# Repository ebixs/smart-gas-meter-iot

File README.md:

<!--
  Smart Gas Meter IoT
  Languages: English | فارسی | Deutsch
-->

<div align="center">

# Smart Gas Meter IoT

### A modular, safety-conscious smart metering research prototype

**Embedded Systems · Custom PCB · Cellular IoT · Automated Billing · Data Analytics**

<p>

</p>

[Overview](#english) · [فارسی](#فارسی) · [Deutsch](#deutsch) · [Architecture](#architecture) · [Safety](#safety)

[Project site](https://ebixs.github.io/smart-gas-meter-iot/) · [Interactive Project Gallery](hardware/visualization/project-gallery.html) · [3D Concept View](hardware/visualization/smart-gas-meter-exploded.html) · [Visual Design Notes](hardware/visualization/README.md) · [Requirements](docs/requirements.md) · [Architecture Details](docs/architecture.md) · [Development API](docs/api-development.md) · [Production Architecture](docs/production-product-architecture.md) · [Design Decisions v1](hardware/design-decisions-v1.md) · [Release Readiness](hardware/release-readiness.md) · [Pinout & Test Points](hardware/pinout-and-testpoints-v0.2.md) · [AI, Billing & Tamper Requirements](docs/ai-billing-and-tamper-requirements.md) · [Telemetry Contract](docs/telemetry-contract.md) · [Telemetry JSON Schema](schemas/telemetry.schema.json) · [Board v0.1 Design](hardware/board-v0.1-design.md) · [Schematic Plan](hardware/board-v0.2-schematic-plan.md) · [Cellular Modem Interface](hardware/modem-daughterboard-interface.md) · [Board BOM](hardware/BOM-board-v0.1.md) · [Board Netlist Draft](hardware/board-v0.1-netlist-draft.csv) · [Native KiCad Schematic v0.2](hardware/kicad/smart_gas_meter_iot.kicad_sch) · [Schematic PDF](hardware/kicad/exports/smart_gas_meter_iot-schematic.pdf) · [CAD Reference Attribution](hardware/kicad/REFERENCE_ATTRIBUTION_AND_STATUS.md) · [v0.2 Netlist Draft](hardware/kicad/board-v0.2-netlist-draft.csv) · [v0.2 PCB Layout Plan](hardware/kicad/board-v0.2-layout-plan.md) · [PCB Layout Checklist](hardware/board-v0.1-layout-checklist.md) · [Bring-up Test Plan](hardware/board-v0.1-bringup-test-plan.md) · [Initial BOM](hardware/BOM-draft.md) · [Pulse Simulator Spec](hardware/pulse-simulator-spec.md) · [Software Simulator](simulator/pulse_simulator.py) · [Send Synthetic Data to API](simulator/push_to_api.py)

</div>

---

## Showcase

<p align="center">
  
  <br>
  <sub><a href="hardware/visualization/media/sgm-launch-film.mp4">30-second film (MP4)</a> · <a href="https://ebixs.github.io/smart-gas-meter-iot/">project site</a> · all data synthetic · bench prototype</sub>
</p>

| | What it is | Where |
|---|---|---|
| **Fleet console** | 240 simulated meters: readings, self-read invoices, forecasts, alerts | [`docs/dashboard`](docs/dashboard/index.html) · [live](https://ebixs.github.io/smart-gas-meter-iot/dashboard/) |
| **How a pulse works** | Interactive isometric figure: drums, reed pulser, cable, SGM display | [`hardware/visualization/anatomy`](hardware/visualization/anatomy/build.mjs) · [live](https://ebixs.github.io/smart-gas-meter-iot/anatomy/pulse-anatomy-light.html) |
| **Invoice check** | Scan an invoice's QR token, see what the issuer billed | [`docs/verify`](docs/verify/index.html) · [live](https://ebixs.github.io/smart-gas-meter-iot/verify/) |
| **Firmware** | ESP32-S3: debounced reed input, power-safe counter, Jalali self-reading, LTE + SMS fallback | [`firmware/`](firmware/README.md) |
| **Analytics & billing** | Fleet simulator, forecasts (WAPE 9.5 %), six fault detectors, bilingual PDF invoices | [`analytics/`](analytics/) · [report](docs/analytics/REPORT.md) |
| **Hardware** | KiCad 9 schematic, routed 4-layer PCB, BOM, v0.3 power/modem decisions | [`hardware/kicad`](hardware/kicad/) · [decisions](docs/hardware-decisions.md) |
| **Film source** | Code-drawn 30 s film, deterministic frame capture | [`media/film`](media/film/BRIEF.md) |

> **Bench only.** The pulse input takes a synthetic 3.3 V signal; never connect a live gas meter, gas line, valve, mains or field wiring. An analytics alert is not proof of a leak. Invoice prices are illustrative.
>
> **فقط روی میز آزمایش.** ورودی پالس فقط سیگنال مصنوعی ۳٫۳ ولت می‌پذیرد؛ هرگز به کنتور، لوله گاز، شیر، برق شهر یا سیم‌کشی میدانی وصل نشود. هشدار تحلیلی اثبات نشت گاز نیست و قیمت‌های قبض نمونه‌اند.

---

## 🇬🇧 English

### Overview

**Smart Gas Meter IoT** is a proposed end-to-end prototype for exploring how embedded electronics, simulated meter pulses, cellular connectivity, and a Python backend can work together to monitor consumption and prepare billing records.

The project is being developed as a practical engineering portfolio: from circuit and PCB design to firmware, data services, a dashboard, and analytics. **Built so far:** KiCad schematic and routed PCB, ESP32-S3 bench firmware, telemetry contract v2 with a batch API, the analytics and billing pipeline, a fleet console and an invoice verification page (see Showcase). **Not done:** a fabricated and flashed board, field trials, any certification. Anything not listed as built is still a plan.

### Current engineering baseline

- ESP32-S3-WROOM-1-N8 is a candidate controller, not a frozen component choice.
- Cellular communication is planned through a separate modem interface so the modem can be selected after checking the target region, operator, bands and certification path.
- The board direction is a larger, test-friendly four-layer design, subject to electrical and layout review.
- Early tests must use synthetic pulses and isolated low-voltage circuits only.
- AI anomaly flags are advisory and cannot establish that a gas leak exists.
- Billing output remains a prototype report until metrology and legal requirements are established.

### Planned capabilities

- Embedded controller, local storage, timekeeping and status indicators.
- Safe pulse simulation without connecting to a live gas meter.
- Cellular telemetry with local queueing and retry after reconnect.
- Python API, database, device records and validation.
- Traceable draft invoices with tariff versioning and QR verification.
- Consumption trends, forecasts, anomaly flags, tamper/fault events and device-health monitoring.
- Engineering documentation, native schematic, PCB layout, 3D assembly views and test plans.

### Development roadmap

- [x] Draft initial requirements and system interfaces.
- [x] Specify simulator acceptance tests and add a software telemetry fixture.
- [x] Add unit tests for the simulator and GitHub Actions CI workflow.
- [x] Define the versioned telemetry contract and JSON Schema.
- [x] Document the initial controller/board concept, cellular interface, product architecture, pinout proposal and release gates.
- [x] Add a standalone interactive isometric concept illustration (not CAD-derived or fabrication-ready).
- [x] Rebuild the native KiCad schematic from a reviewed design table (v0.2): KiCad 9 ERC 0 errors / 0 warnings, exported netlist checked pin-by-pin against the design.
- [x] Select exact, orderable parts (MPN + LCSC) checked against datasheets; schematic freeze candidate v0.2-rc1 ([part selection](hardware/kicad/PART_SELECTION.md)).
- [ ] Second-engineer sign-off of the schematic freeze.
- [x] Create a routed 4-layer KiCad PCB from the schematic: KiCad 9 DRC 0 violations / 0 unconnected / 0 schematic-parity issues, with CAD-derived 3D renders ([PCB design](hardware/kicad/PCB_DESIGN.md)).
- [ ] Hand-tune the USB pair, review the power layout and DFM, and get second-engineer sign-off before ordering boards.
- [ ] Complete BOM with exact parts, footprints and approved alternates.
- [x] Run electrical-rule and design-rule checks (ERC and DRC clean; reports in `hardware/kicad/exports/`).
- [x] Export Gerbers, drill, BOM and pick-and-place files as **review artefacts** (not released for fabrication).
- [x] Add a development-only FastAPI + SQLite ingestion API with duplicate-safe records, bearer-token protection, pulse-delta reporting and a local dashboard (`/dashboard`).
- [ ] Add per-device identity/credentials, production database hardening, firmware, billing and analytics.
- [ ] Run recorded low-voltage bench tests and later region-specific radio validation.
- [ ] Complete qualified safety, metrology, EMC, radio, cybersecurity and regulatory reviews.

---

## 🇮🇷 فارسی

<div dir="rtl" align="right">

### معرفی پروژه

**کنتور گاز هوشمند اینترنت اشیا (Smart Gas Meter IoT)** پروژه‌ای برای ارتقای یک ایده سخت‌افزاری قدیمی با رویکرد مهندسی جدید است؛ از طراحی برد و ارتباط سلولی تا ثبت داده، تحلیل مصرف و تولید گزارش صورتحساب.

### تصمیم‌های طراحی فعلی

- میکروکنترلر ESP32-S3-WROOM-1-N8 گزینه اولیه است و تا بررسی مدار نهایی، قطعه قطعی محسوب نمی‌شود.
- مودم سیم‌کارتی به‌صورت ماژول جداشدنی طراحی می‌شود تا انتخاب مدل به پوشش شبکه، اپراتور، باندها و تأییدیه‌ها وابسته بماند.
- جهت طراحی برد، نمونه‌ای بزرگ‌تر و چهارلایه با نقاط تست فراوان است؛ تعداد لایه‌ها و ابعاد پس از طراحی و بررسی نهایی می‌شود.
- آزمون اولیه فقط با پالس مصنوعی و مدار کم‌ولتاژ ایزوله انجام می‌شود.
- تحلیل ناهنجاری مصرف به‌تنهایی اثبات‌کننده نشت گاز نیست.
- صورتحساب تا تعیین الزامات قانونی و اندازه‌گیری، گزارش آزمایشی است.

### وضعیت واقعی پروژه

مستندات معماری، نیازمندی‌ها، رابط مودم، نگاشت اولیه پایه‌ها و برنامه آمادگی ساخت در مخزن قرار گرفته‌اند. شماتیک بومی KiCad نسخه v0.2 به‌صورت کنترل‌شده از نو ساخته شده و ERC آن بدون خطاست. PCB چهارلایه هم از روی همین شماتیک مسیرکشی شده و DRC آن بدون خطا و کاملاً منطبق با شماتیک است. با این حال **فایل‌های ساخت فقط برای بازبینی هستند** و پیش از سفارش، مسیر USB، چیدمان تغذیه و بررسی مهندس دوم باید تکمیل شود؛ بنابراین پروژه هنوز آماده سفارش PCB یا مونتاژ نیست.

### نقشه راه

- [x] تدوین نیازمندی‌ها، معماری و قرارداد داده.
- [x] ساخت شبیه‌ساز نرم‌افزاری، ابزار ارسال داده مصنوعی به API و آزمون‌های خودکار.
- [x] مستندسازی تصمیم‌های اولیه برد، رابط مودم، نقاط تست و معیارهای آماده‌سازی ساخت.
- [x] افزودن API آزمایشی FastAPI و SQLite با توکن دسترسی، جلوگیری از تکرار، گزارش اختلاف شمارنده پالس و داشبورد محلی (`/dashboard`).
- [ ] افزودن هویت و اعتبارنامه مستقل برای هر دستگاه، سخت‌سازی پایگاه داده، فریم‌ور و صورتحساب واقعی.
- [x] بازسازی شماتیک بومی KiCad از جدول طراحی (v0.2): ERC در KiCad 9 بدون خطا و هشدار، و تطبیق پایه‌به‌پایه نت‌لیست با طراحی.
- [x] انتخاب قطعات دقیق و قابل سفارش (MPN و کد LCSC) با بررسی دیتاشیت؛ نسخه‌ی کاندید فریز شماتیک v0.2-rc1.
- [ ] تأیید نهایی فریز شماتیک توسط یک مهندس دوم.
- [x] طراحی و مسیرکشی PCB چهارلایه و بررسی DRC (بدون خطا، بدون اتصال باز و منطبق با شماتیک).
- [x] استخراج نمای سه‌بعدی از مدل واقعی PCB.
- [ ] تکمیل BOM، فوت‌پرینت‌ها و قطعات جایگزین.
- [x] تولید Gerber، فایل سوراخ‌کاری و فایل‌های مونتاژ برای بازبینی (هنوز برای سفارش ساخت تأیید نشده).
- [ ] اجرای آزمون‌های ثبت‌شده با مدار کم‌ولتاژ.
- [ ] ارزیابی تخصصی ایمنی، اندازه‌گیری، رادیویی، EMC و مقررات پیش از استفاده عملیاتی.

</div>

---

## 🇩🇪 Deutsch

Smart Gas Meter IoT is a modular engineering prototype for simulated pulse acquisition, cellular telemetry, data analysis and draft billing. The repository documents the intended design and separates documented proposals from implemented and verified hardware.

The current baseline proposes an ESP32-S3 controller, a modular cellular interface and a larger test-friendly PCB. A development-only FastAPI + SQLite service and local dashboard now accept/view synthetic telemetry, require a shared bearer token for data endpoints, and reject conflicting duplicate sequences. It is not production-secure and does not yet provide per-device credentials. A rebuilt native KiCad schematic (freeze candidate v0.2-rc1, exact parts selected) passes KiCad 9 ERC with no violations, but awaits second-engineer sign-off; a routed 4-layer PCB passes DRC with schematic parity and has CAD-derived 3D renders; Gerbers exist as review artefacts only, pending USB-pair tuning, power-layout/DFM review and sign-off. Only isolated low-voltage laboratory tests using synthetic pulses are in scope at this stage.

---

## System architecture / معماری سیستم

```mermaid
flowchart LR
    A["Pulse Simulator"] --> B["Embedded Controller"]
    B --> C["Local Storage"]
    B --> D["Cellular IoT"]
    D --> E["Python API"]
    E --> F[("Database")]
    F --> G["Billing Service"]
    F --> H["Dashboard & Analytics"]
```

This is the planned architecture, not a claim that all components have been implemented.

## Safety and scope / ایمنی

- Laboratory prototype only. Use simulated pulses and low-voltage test circuits.
- Do not connect this prototype to a live gas line, operational meter, mains wiring or unknown field signals.
- This project is not a certified measuring instrument, leak detector, billing authority or safety device.
- Real deployment requires qualified review and applicable metrology, gas-safety, radio, EMC, cybersecurity and local regulatory compliance.
- No component ordering or fabrication is authorized without explicit owner approval.

## Project history / سابقه پروژه

In 1396 SH (2017–2018), the project owner personally designed and built an original smart gas meter prototype for Iran Gas Company in Shahrekord, Chaharmahal and Bakhtiari Province, Iran. This repository documents a modernized development effort; historical work must not be confused with new features that remain unimplemented or untested.

## License

No license has been selected yet. Until a license is added, the repository should not be assumed to grant permission to reuse, modify or distribute its contents.

### v0.2 hardware design drafts
- [PCB design & 3D renders](hardware/kicad/PCB_DESIGN.md) · [DRC report](hardware/kicad/exports/pcb/drc-kicad-9.rpt) · [Gerbers (review only)](hardware/kicad/exports/pcb/gerbers/)
- [Native schematic v0.2-rc1 (PDF)](hardware/kicad/exports/smart_gas_meter_iot-schematic.pdf) · [KiCad ERC report](hardware/kicad/exports/erc-kicad-9.0.3.rpt) · [BOM](hardware/kicad/exports/BOM-v0.2-rc1.md) · [JLCPCB BOM (CSV)](hardware/kicad/exports/BOM-v0.2-rc1-jlcpcb.csv) · [Part selection](hardware/kicad/PART_SELECTION.md)
- [Design table — single source of truth](hardware/kicad/design_v02.py) and [how the schematic is generated and verified](hardware/kicad/README.md)
- [Candidate pin-to-net map (CSV)](hardware/kicad/board-v0.2-netlist-draft.csv)
- [PCB placement and routing plan](hardware/kicad/board-v0.2-layout-plan.md)
- [Native KiCad delivery gate](hardware/kicad/NATIVE_CAD_DELIVERY_GATE.md)

Schematic (ERC-clean) and routed PCB (DRC-clean, schematic parity) exist for review. Fabrication still waits on USB-pair tuning, power-layout/DFM review, land-pattern checks and sign-off.

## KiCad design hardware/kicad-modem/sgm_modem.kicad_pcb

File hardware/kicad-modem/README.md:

# Modem daughterboard v0.1 — Quectel EC200U-EU (KiCad)

**Status: v0.1-draft — engineering draft, NOT fabrication ready.** The schematic follows the Quectel EC200U Series
Hardware Design V1.0; the PCB is a 4-layer layout study. **The EC200U footprint is provisional**: its pad geometry and
the pad that carries each pin number are placeholders built from the partial dimensions in the hardware design guide.
It must be replaced by Quectel's *EC200U Series Footprint & Part* file, and the board re-placed and re-routed, before
any layout review or order. Bench-only: `MODEM_VIN` comes from a current-limited 3.8 V supply. Never connect any of
this to a live gas meter, gas line, valve, mains or field wiring.

The board plugs onto the carrier board's modem header **J6** (carrier v0.2, `hardware/kicad/`) with a socket **J1**
on its underside, pin for pin: `1 MODEM_VIN · 2 GND · 3 MODEM_TXD · 4 MODEM_RXD · 5 MODEM_EN · 6 MODEM_RESET ·
7 MODEM_STATUS · 8 GND` (3.3 V logic). It is the "replaceable modem board" of the hardware decisions.

## What is here

| Path | Purpose |
|---|---|
| `design_modem_v01.py` | **Single source of truth**: every part, value, footprint and pin → net assignment (same `Part` API as the carrier's `design_v02.py`) |
| `tools/generate_schematic.py` | Writes the schematic, project file and project-local libraries; reuses the carrier's sheet writer unchanged; generates the `EC200U` symbol and the **provisional** footprint |
| `sgm_modem.kicad_sch` / `.kicad_pro` | Native KiCad schematic (KiCad 7 format; opens in KiCad 7, 8, 9) |
| `lib/sgm_modem.kicad_sym`, `lib/SGMM.pretty/`, `lib/3d/` | Project-local symbols, footprints and STEP models (nickname `SGMM`) |
| `pcb_layout_modem_v01.py` | Placement table (75 × 50 mm, 4 layers) |
| `tools/build_pcb.py` | Builds the board with KiCad's `pcbnew` module, fans ground and VBAT pads out to their planes, autoroutes with Freerouting, stitches the ground pours and writes a DRC report |
| `sgm_modem.kicad_pcb` | The routed layout study |
| `check_netlist_matches_design.py` | Netlist vs. design, pin by pin, plus J1 pin-out = carrier J6 |
| `tests/` | Design invariants (no 3V3 on the modem, open-collector PWRKEY/RESET_N, every 1.8 V output shifted, …) |
| `exports/` | Schematic PDF, netlist, DRC report, layer artwork |

## Circuit (from the EC200U hardware design guide)

1. **VBAT** — `MODEM_VIN` (3.3–4.3 V, 3.8 V nominal, up to 2 A bursts) feeds VBAT_RF (57, 58) and VBAT_BB (59, 60).
   Two 100 µF low-ESR tantalum capacitors, a 100 nF / 33 pF / 10 pF MLCC set at each pin pair, and a TVS diode with
   ≥ 4.7 V stand-off (to be selected). On the PCB the whole inner layer In2 is the VBAT plane (the guide asks for
   ≥ 2–2.5 mm VBAT traces). J2 is an optional direct VBAT input, not fitted: never run it in parallel with carrier J7.
2. **PWRKEY / RESET_N** — open-collector MMBT3904 drivers (4.7 kΩ base resistor, 47 kΩ base pull-down) from
   `MODEM_EN` / `MODEM_RESET`. The carrier's 100 kΩ pull-downs keep the module off while the ESP32 boots.
   Switching on or off needs PWRKEY low for ≥ 2 s.
3. **Level shifting** — the module's UART and STATUS are 1.8 V. Three N-MOSFET shifters with their gates on
   `VDD_EXT` (the module's own 1.8 V output, 2.2 µF) and 10 kΩ pull-ups on the 1.8 V side. Candidate FET:
   Diodes DMG2302U (V<sub>GS(th)</sub> ≤ 1.0 V); a BSS138 is marginal with a 1.8 V gate.
4. **(U)SIM** — JAE SF53S006VCBR2000 micro-SIM, 0 Ω series resistors, 33 pF on each line, 10 kΩ pull-up on DATA,
   100 nF on USIM_VDD and a TI ESD224 array (0.5 pF; the guide's limit is 15 pF).
5. **Antenna** — ANT_MAIN on a short 50 Ω line (net class RF, 0.35 mm over the In1 ground plane — confirm with the
   fabricator's stack-up) to a Hirose u.FL, with a π network (0 Ω + two not-mounted shunts).
6. **Network LED** — NET_STATUS drives a green LED through a transistor, about 1.8 mA from VBAT.
7. **Bench access** — test pads for the module USB (VBUS, D+, D−) and the 1.8 V debug UART; solder jumper JP1 with
   4.7 kΩ to `VDD_EXT` forces USB download mode when closed before power-up (open by default).

## Review items (open)

- **Footprint**: replace the provisional EC200U footprint with Quectel's file; then re-place and re-route.
- **MCU-side pull-ups**: J6 carries no 3.3 V rail, so `MODEM_RXD` and `MODEM_STATUS` rely on the ESP32's internal
  pull-ups (firmware must enable them). Alternative: add 3V3 to the next carrier revision's modem header.
- **TVS selection** for VBAT, exact MPNs for the tantalum capacitors and the MOSFETs.
- **Header current**: one 2.54 mm pin carries `MODEM_VIN` bursts of up to 2 A; check the socket rating or use J2.
- **RF line width** against the real stack-up; tune the π network with the chosen antenna.

## Verification (2026-10-26, KiCad 7.0.11 here; CI repeats ERC/DRC with KiCad 9)

| Check | Result |
|---|---|
| Netlist vs. design (`check_netlist_matches_design.py`) | 55 parts, 35 nets, 190 pin connections match; J1 = carrier J6 |
| Schematic ↔ design sync (`generate_schematic.py --check`) | committed file matches a fresh generation |
| Design invariants (`python3 -m unittest discover -s hardware/kicad-modem/tests`) | pass |
| DRC (KiCad 7 `pcbnew`, `exports/drc-kicad-7.rpt`) | 0 violations, 0 unconnected pads |
| ERC + DRC with schematic parity, KiCad 9 (CI `hardware-cad-check.yml`, PR #8) | ERC pass; DRC 0 violations, 0 unconnected, 0 footprint errors |

A clean DRC here only proves the layout is consistent with the **provisional** footprint; it says nothing about the real module pads.

## Regenerate

```bash
python3 hardware/kicad-modem/tools/generate_schematic.py [--kicad-3d /path/to/kicad-packages3D]
python3 hardware/kicad-modem/tools/build_pcb.py --route          # needs Java 21 and freerouting.jar (v2.1)
kicad-cli sch export netlist -o /tmp/modem.net hardware/kicad-modem/sgm_modem.kicad_sch
python3 hardware/kicad-modem/check_netlist_matches_design.py /tmp/modem.net
python3 -m unittest discover -s hardware/kicad-modem/tests
```

The board's exploded 3D model is in `hardware/visualization/boards/modem.html`, and the schematic can be explored
net by net in `hardware/visualization/schematic/index.html`.

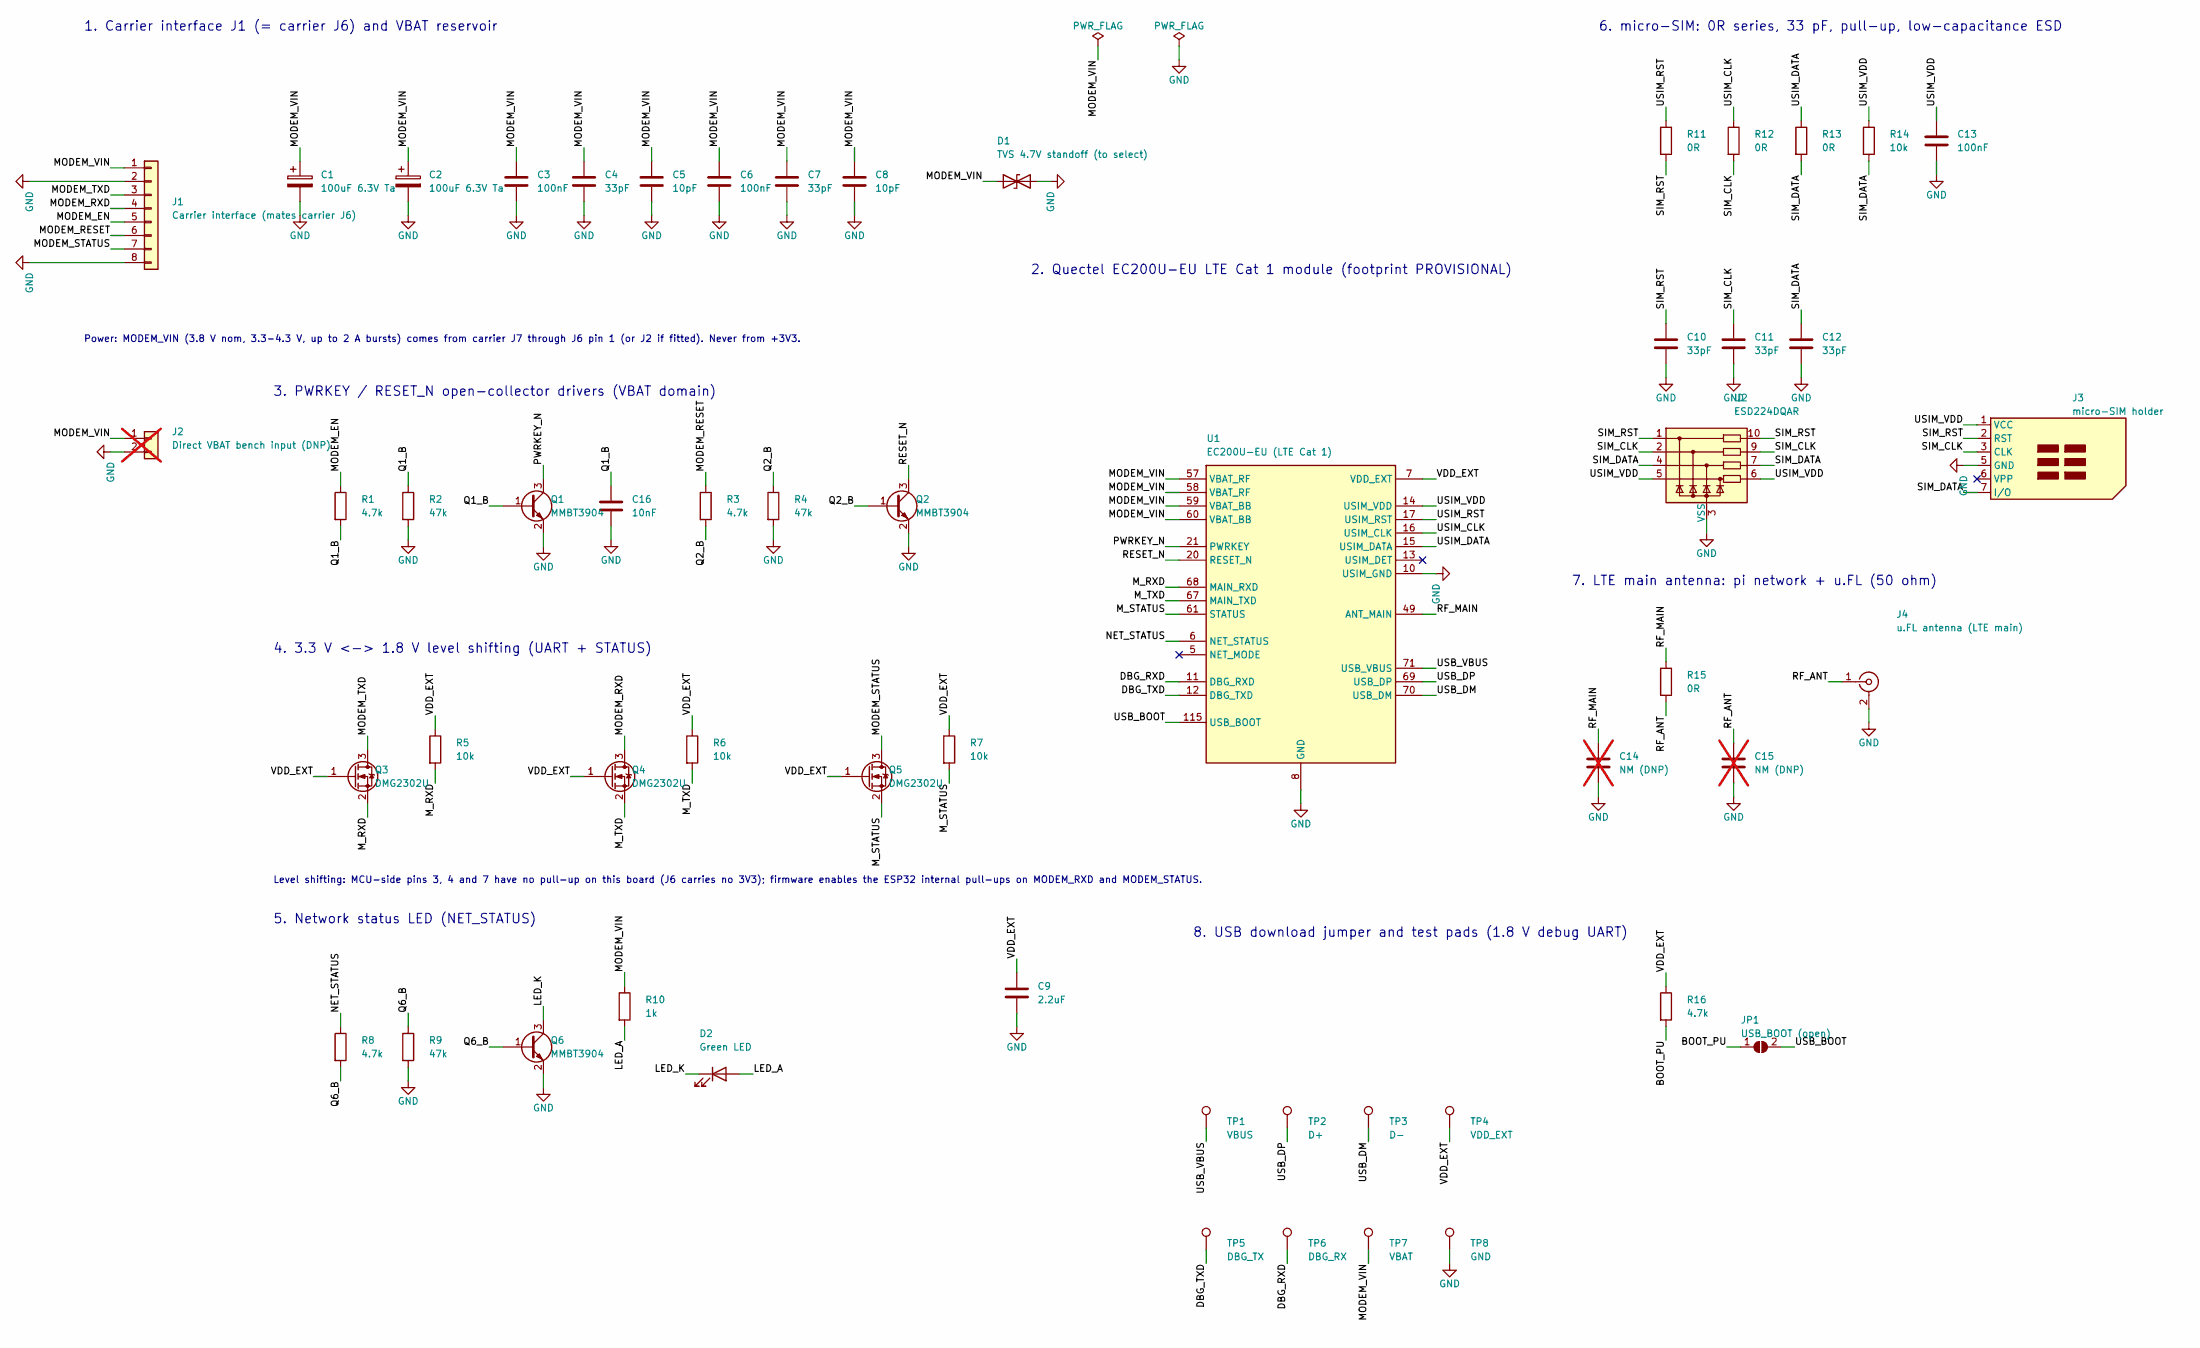
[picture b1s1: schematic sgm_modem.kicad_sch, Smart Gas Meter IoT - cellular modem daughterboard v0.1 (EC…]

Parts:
C1, C2: 100uF 6.3V Ta; CP_EIA-3528-21_Kemet-B; MPN TBD
C3, C6, C13: 100nF; C_0402_1005Metric; MPN TBD
C4, C7, C10, C11, C12: 33pF; C_0402_1005Metric; MPN TBD
C5, C8: 10pF; C_0402_1005Metric; MPN TBD
C9: 2.2uF; C_0402_1005Metric; MPN TBD
C14, C15: NM (DNP); C_0402_1005Metric; MPN TBD; not fitted
C16: 10nF; C_0402_1005Metric; MPN TBD
D1: TVS 4.7V standoff (to select); D_SMB; MPN TBD
D2: Green LED; LED_0603_1608Metric; MPN TBD
J1: Carrier interface (mates carrier J6); PinSocket_1x08_P2.54mm_Vertical; MPN generic
J2: Direct VBAT bench input (DNP); PinHeader_1x02_P2.54mm_Vertical; MPN generic; not fitted
J3: micro-SIM holder; microSIM_JAE_SF53S006VCBR2000; MPN JAE SF53S006VCBR2000
J4: u.FL antenna (LTE main); U.FL_Hirose_U.FL-R-SMT-1_Vertical; MPN Hirose U.FL-R-SMT-1
JP1: USB_BOOT (open); SolderJumper-2_P1.3mm_Open_RoundedPad1.0x1.5mm; MPN generic
Q1, Q2, Q6: MMBT3904; SOT-23; MPN TBD
Q3, Q4, Q5: DMG2302U; SOT-23; MPN TBD
R1, R3, R8, R16: 4.7k; R_0402_1005Metric; MPN TBD
R2, R4, R9: 47k; R_0402_1005Metric; MPN TBD
R5, R6, R7, R14: 10k; R_0402_1005Metric; MPN TBD
R10: 1k; R_0402_1005Metric; MPN TBD
R11, R12, R13, R15: 0R; R_0402_1005Metric; MPN TBD
TP1: VBUS; TestPoint_Pad_D1.0mm; MPN generic
TP2: D+; TestPoint_Pad_D1.0mm; MPN generic
TP3: D-; TestPoint_Pad_D1.0mm; MPN generic
TP4: VDD_EXT; TestPoint_Pad_D1.0mm; MPN generic
TP5: DBG_TX; TestPoint_Pad_D1.0mm; MPN generic
TP6: DBG_RX; TestPoint_Pad_D1.0mm; MPN generic
TP7: VBAT; TestPoint_Pad_D1.0mm; MPN generic
TP8: GND; TestPoint_Pad_D1.0mm; MPN generic
U1: EC200U-EU (LTE Cat 1); Quectel_EC200U_PROVISIONAL; MPN Quectel EC200U-EU (candidate)
U2: ESD224DQAR; USON-10_2.5x1.0mm_P0.5mm; MPN Texas Instruments ESD224DQAR (candidate)

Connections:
/BOOT_PU: JP1.1 (A), R16.2
/DBG_RXD: TP6.1, U1.11 (DBG_RXD)
/DBG_TXD: TP5.1, U1.12 (DBG_TXD)
/LED_A: D2.2 (A), R10.2
/LED_K: D2.1 (K), Q6.3 (C)
/MODEM_EN: J1.5, R1.1
/MODEM_RESET: J1.6, R3.1
/MODEM_RXD: J1.4, Q4.3 (D)
/MODEM_STATUS: J1.7, Q5.3 (D)
/MODEM_TXD: J1.3, Q3.3 (D)
/MODEM_VIN: C1.1, C2.1, C3.1, C4.1, C5.1, C6.1, C7.1, C8.1, D1.1 (A1), J1.1, J2.1, R10.1, TP7.1, U1.57 (VBAT_RF), U1.58 (VBAT_RF), U1.59 (VBAT_BB), U1.60 (VBAT_BB)
/M_RXD: Q3.2 (S), R5.2, U1.68 (MAIN_RXD)
/M_STATUS: Q5.2 (S), R7.2, U1.61 (STATUS)
/M_TXD: Q4.2 (S), R6.2, U1.67 (MAIN_TXD)
/NET_STATUS: R8.1, U1.6 (NET_STATUS)
/PWRKEY_N: Q1.3 (C), U1.21 (PWRKEY)
/Q1_B: C16.1, Q1.1 (B), R1.2, R2.1
/Q2_B: Q2.1 (B), R3.2, R4.1
/Q6_B: Q6.1 (B), R8.2, R9.1
/RESET_N: Q2.3 (C), U1.20 (RESET_N)
/RF_ANT: C15.1, J4.1 (In), R15.2
/RF_MAIN: C14.1, R15.1, U1.49 (ANT_MAIN)
/SIM_CLK: C11.1, J3.3 (CLK), R12.2, U2.2, U2.9
/SIM_DATA: C12.1, J3.7 (I/O), R13.2, R14.2, U2.4, U2.7
/SIM_RST: C10.1, J3.2 (RST), R11.2, U2.1, U2.10
/USB_BOOT: JP1.2 (B), U1.115 (USB_BOOT)
/USB_DM: TP3.1, U1.70 (USB_DM)
/USB_DP: TP2.1, U1.69 (USB_DP)
/USB_VBUS: TP1.1, U1.71 (USB_VBUS)
/USIM_CLK: R12.1, U1.16 (USIM_CLK)
/USIM_DATA: R13.1, U1.15 (USIM_DATA)
/USIM_RST: R11.1, U1.17 (USIM_RST)
/USIM_VDD: C13.1, J3.1 (VCC), R14.1, U1.14 (USIM_VDD), U2.5, U2.6
/VDD_EXT: C9.1, Q3.1 (G), Q4.1 (G), Q5.1 (G), R5.1, R6.1, R7.1, R16.1, TP4.1, U1.7 (VDD_EXT)
GND: C1.2, C2.2, C3.2, C4.2, C5.2, C6.2, C7.2, C8.2, C9.2, C10.2, C11.2, C12.2, C13.2, C14.2, C15.2, C16.2, D1.2 (A2), J1.2, J1.8, J2.2, J3.5 (GND), J3.SH, J4.2 (Ext), Q1.2 (E), Q2.2 (E), Q6.2 (E), R2.2, R4.2, R9.2, TP8.1, U1.8 (GND), U1.9 (GND), U1.10 (USIM_GND), U1.19 (GND), U1.22 (GND), U1.36 (GND), U1.46 (GND), U1.48 (GND), U1.50 (GND), U1.51 (GND), U1.52 (GND), U1.53 (GND), U1.54 (GND), U1.56 (GND), U1.72 (GND), U1.76 (GND), U1.85 (GND), U1.86 (GND), U1.87 (GND), U1.88 (GND), U1.89 (GND), U1.90 (GND), U1.91 (GND), U1.92 (GND), U1.93 (GND), U1.94 (GND), U1.95 (GND), U1.96 (GND), U1.97 (GND), U1.98 (GND), U1.99 (GND), U1.100 (GND), U1.101 (GND), U1.102 (GND), U1.103 (GND), U1.104 (GND), U1.105 (GND), U1.106 (GND), U1.107 (GND), U1.108 (GND), U1.109 (GND), U1.110 (GND), U1.111 (GND), U1.112 (GND), U2.3 (VSS), U2.8 (VSS)

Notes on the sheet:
1. Carrier interface J1 (= carrier J6) and VBAT reservoir
2. Quectel EC200U-EU LTE Cat 1 module (footprint PROVISIONAL)
3. PWRKEY / RESET_N open-collector drivers (VBAT domain)
4. 3.3 V <-> 1.8 V level shifting (UART + STATUS)
5. Network status LED (NET_STATUS)
6. micro-SIM: 0R series, 33 pF, pull-up, low-capacitance ESD
7. LTE main antenna: pi network + u.FL (50 ohm)
8. USB download jumper and test pads (1.8 V debug UART)
Power: MODEM_VIN (3.8 V nom, 3.3-4.3 V, up to 2 A bursts) comes from carrier J7 through J6 pin 1 (or J2 if fitted). Never from +3V3.
Level shifting: MCU-side pins 3, 4 and 7 have no pull-up on this board (J6 carries no 3V3); firmware enables the ESP32 internal pull-ups on MODEM_RXD and MODEM_STATUS.

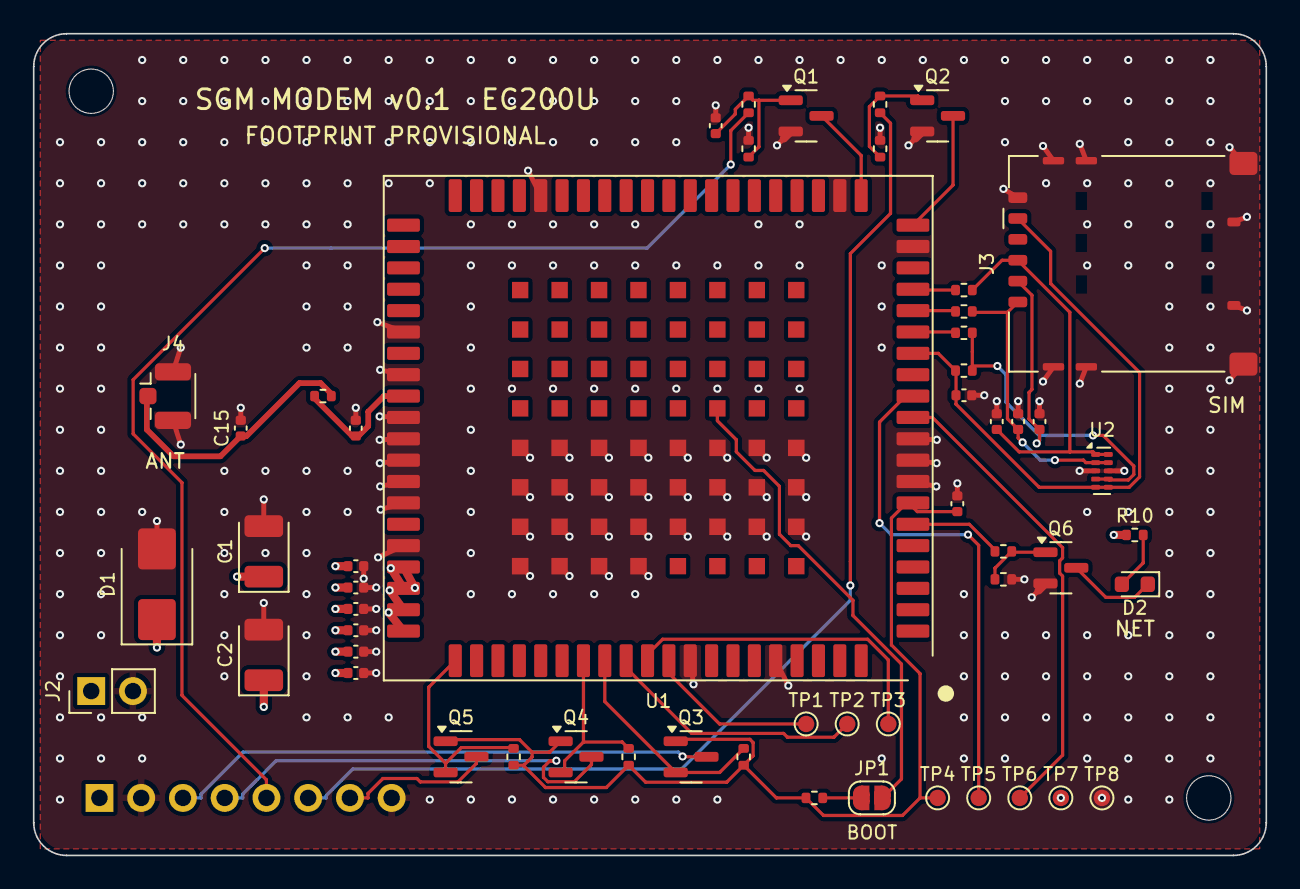
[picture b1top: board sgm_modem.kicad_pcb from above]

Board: 4 copper layers, 75.0 x 50.0 mm, 57 parts (1 on the bottom side), 35 nets.

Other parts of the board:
H1, H2: M2.5; MountingHole_2.7mm_M2.5

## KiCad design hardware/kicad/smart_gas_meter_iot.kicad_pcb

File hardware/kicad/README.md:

# Native KiCad project — carrier board v0.2

**Status: v0.2-rc1 — schematic freeze candidate with exact parts selected ([PART_SELECTION.md](PART_SELECTION.md)). ERC-clean; awaiting second-engineer sign-off. Routed 4-layer PCB is DRC-clean with schematic parity ([PCB_DESIGN.md](PCB_DESIGN.md)); not released for fabrication.**
Bench-only prototype: current-limited low-voltage supply and a synthetic 3.3 V pulse source. Never connect it to a live gas meter, gas line, valve, mains or field wiring.

## What is here

| Path | Purpose |
|---|---|
| `design_v02.py` | **Single source of truth**: every part, value, footprint, selected MPN/LCSC code and pin → net assignment |
| `tools/generate_schematic.py` | Generates the schematic, project file and project-local libraries from `design_v02.py` |
| `smart_gas_meter_iot.kicad_sch` / `.kicad_pro` | Native KiCad schematic (KiCad 7 file format; opens in KiCad 7, 8 and 9) |
| `lib/smart_gas_meter.kicad_sym`, `lib/SGM.pretty/` | Project-local copies of the KiCad 7.0.11 stock symbols/footprints actually used, so CI needs no global libraries |
| `sym-lib-table`, `fp-lib-table` | Project library tables (nickname `SGM`) |
| `tools/export_bom.py` | Writes the review BOM and the JLCPCB assembly BOM from `design_v02.py` |
| `check_netlist_matches_design.py` | Compares a KiCad-exported netlist with `design_v02.py`, pin by pin |
| `check_netlist_invariants.py` | Guardrail for the blocking faults found in the frozen draft (GND on supply rails, shorted capacitors, legacy dev-board headers, modem on 3V3) |
| `pcb_layout_v02.py`, `tools/build_pcb.py` | PCB placement table and KiCad 9 build/autoroute script |
| `smart_gas_meter_iot.kicad_pcb` | Routed 4-layer PCB (source of truth for copper) |
| `tools/export_pcb.sh` | DRC with schematic parity, Gerbers, drill, CPL, layer PDFs, 3D renders → `exports/pcb/` |
| `lib/3d/` | STEP models for every footprint (paths use `${KIPRJMOD}`) |
| `exports/` | Schematic PDF/PNG, KiCad 9 ERC report, exported netlist and review/JLCPCB BOMs for `v0.2-rc1` |
| `archive/v0.2-frozen-2026-10-23/` | The frozen first draft, kept unchanged as evidence (65 ERC messages, +5V/GND short) |

## Circuit summary

1. **USB-C input** — USB 2.0 receptacle (J1), 5.1 kΩ Rd on CC1 and CC2 separately (R1/R2), PTC fuse (F1) from `USB_VBUS` to `+5V`, TVS (D1) on `+5V`, USBLC6-2SC6 ESD array (U2) on D+/D−.
2. **3V3 buck** — AP63203WU-7 (U3) with the datasheet typical application: 10 µF input, 3.9 µH inductor, 2 × 22 µF output, 100 nF bootstrap; EN tied to VIN.
3. **ESP32-S3-WROOM-1-N8** (U1) — 10 µF + 100 nF at 3V3; EN RC 10 kΩ/1 µF per Espressif guidelines; RESET (SW1) and BOOT/GPIO0 (SW2) buttons; native USB on GPIO19/GPIO20.
4. **Synthetic pulse input** (J2 → GPIO4) — 10 kΩ pull-up, 1 kΩ series resistor, optional DNP filter capacitor. 3.3 V logic or dry contact only.
5. **Status LED** on GPIO5. 6. **Tamper switch** input on GPIO15 with pull-up and RC debounce (advisory event only).
7. **I2C expansion** (GPIO6/7, 4.7 kΩ pull-ups) and **debug UART0** header (no power pin, to avoid back-feeding).
8. **Modem daughterboard connector** (J6) — UART on GPIO17/18, EN/RESET/STATUS on GPIO9/10/11 with safe-default pull-downs. `MODEM_VIN` comes from its own bench-supply connector (J7) and is **never** connected to `+3V3`.
9. **Test points** for 5V, 3V3, VBUS, VMODEM, GND (×2), PULSE_IN, EN and BOOT.

Distinct rails in the netlist: `USB_VBUS`, `+5V`, `+3V3`, `GND`, `MODEM_VIN`. Unused module GPIOs carry explicit no-connect flags (strapping pins GPIO3/45/46 stay at their default state).

## Verification evidence (2026-10-24)

| Check | Tool | Result |
|---|---|---|
| ERC | KiCad 9.0.3 `kicad-cli sch erc --exit-code-violations` | **0 errors, 0 warnings**, no exclusions or rule changes ([report](exports/erc-kicad-9.0.3.rpt)) |
| Netlist vs. design | `check_netlist_matches_design.py` | 48 parts, 28 nets, 135 pin connections match; NC pins match exactly |
| Electrical invariants | `check_netlist_invariants.py` | pass (the same checker reports 10 findings on the archived frozen draft) |
| Schematic ↔ design sync | `generate_schematic.py --check` | committed file is byte-identical to a fresh generation |

The CI workflow `hardware-cad-check.yml` repeats all four checks with KiCad 9 on every push that touches `hardware/kicad/`.

## Regenerate and verify locally

```bash
python3 hardware/kicad/tools/generate_schematic.py          # rewrite schematic + libraries from design_v02.py
python3 hardware/kicad/tools/export_bom.py                  # review BOM + JLCPCB BOM
kicad-cli sch erc --exit-code-violations hardware/kicad/smart_gas_meter_iot.kicad_sch   # KiCad 8/9
kicad-cli sch export netlist -o /tmp/sgm.net hardware/kicad/smart_gas_meter_iot.kicad_sch
python3 hardware/kicad/check_netlist_matches_design.py /tmp/sgm.net
python3 hardware/kicad/check_netlist_invariants.py /tmp/sgm.net
python3 -m unittest discover -s hardware/kicad/tests
```

To change the circuit, edit `design_v02.py`, regenerate, and commit the schematic, libraries and exports together. Hand edits in the KiCad editor are possible, but they must then be reflected back into `design_v02.py`, or the sync check fails.

## Status of the freeze

Exact parts, ratings and pinout checks are recorded in [PART_SELECTION.md](PART_SELECTION.md). The electrical freeze checklist in `SCHEMATIC_ERC_TRIAGE_AND_FREEZE.md` is complete apart from two items. One is the land-pattern overlay against manufacturer drawings, done at PCB stage. The other is the second-engineer sign-off. The modem SKU is deliberately still open: J6 is an interface placeholder.

The PCB has been created from this exact revision; see [PCB_DESIGN.md](PCB_DESIGN.md) for its checks and the review items left before fabrication.

## Library licence

Symbols and footprints are copied from the KiCad 7.0.11 stock libraries (CC-BY-SA 4.0 with the KiCad library exception that permits use in designs without affecting the design's own licence). The archived frozen draft was adapted from MIT-licensed 74th/esp32-dev-boards material; see `REFERENCE_ATTRIBUTION_AND_STATUS.md`.

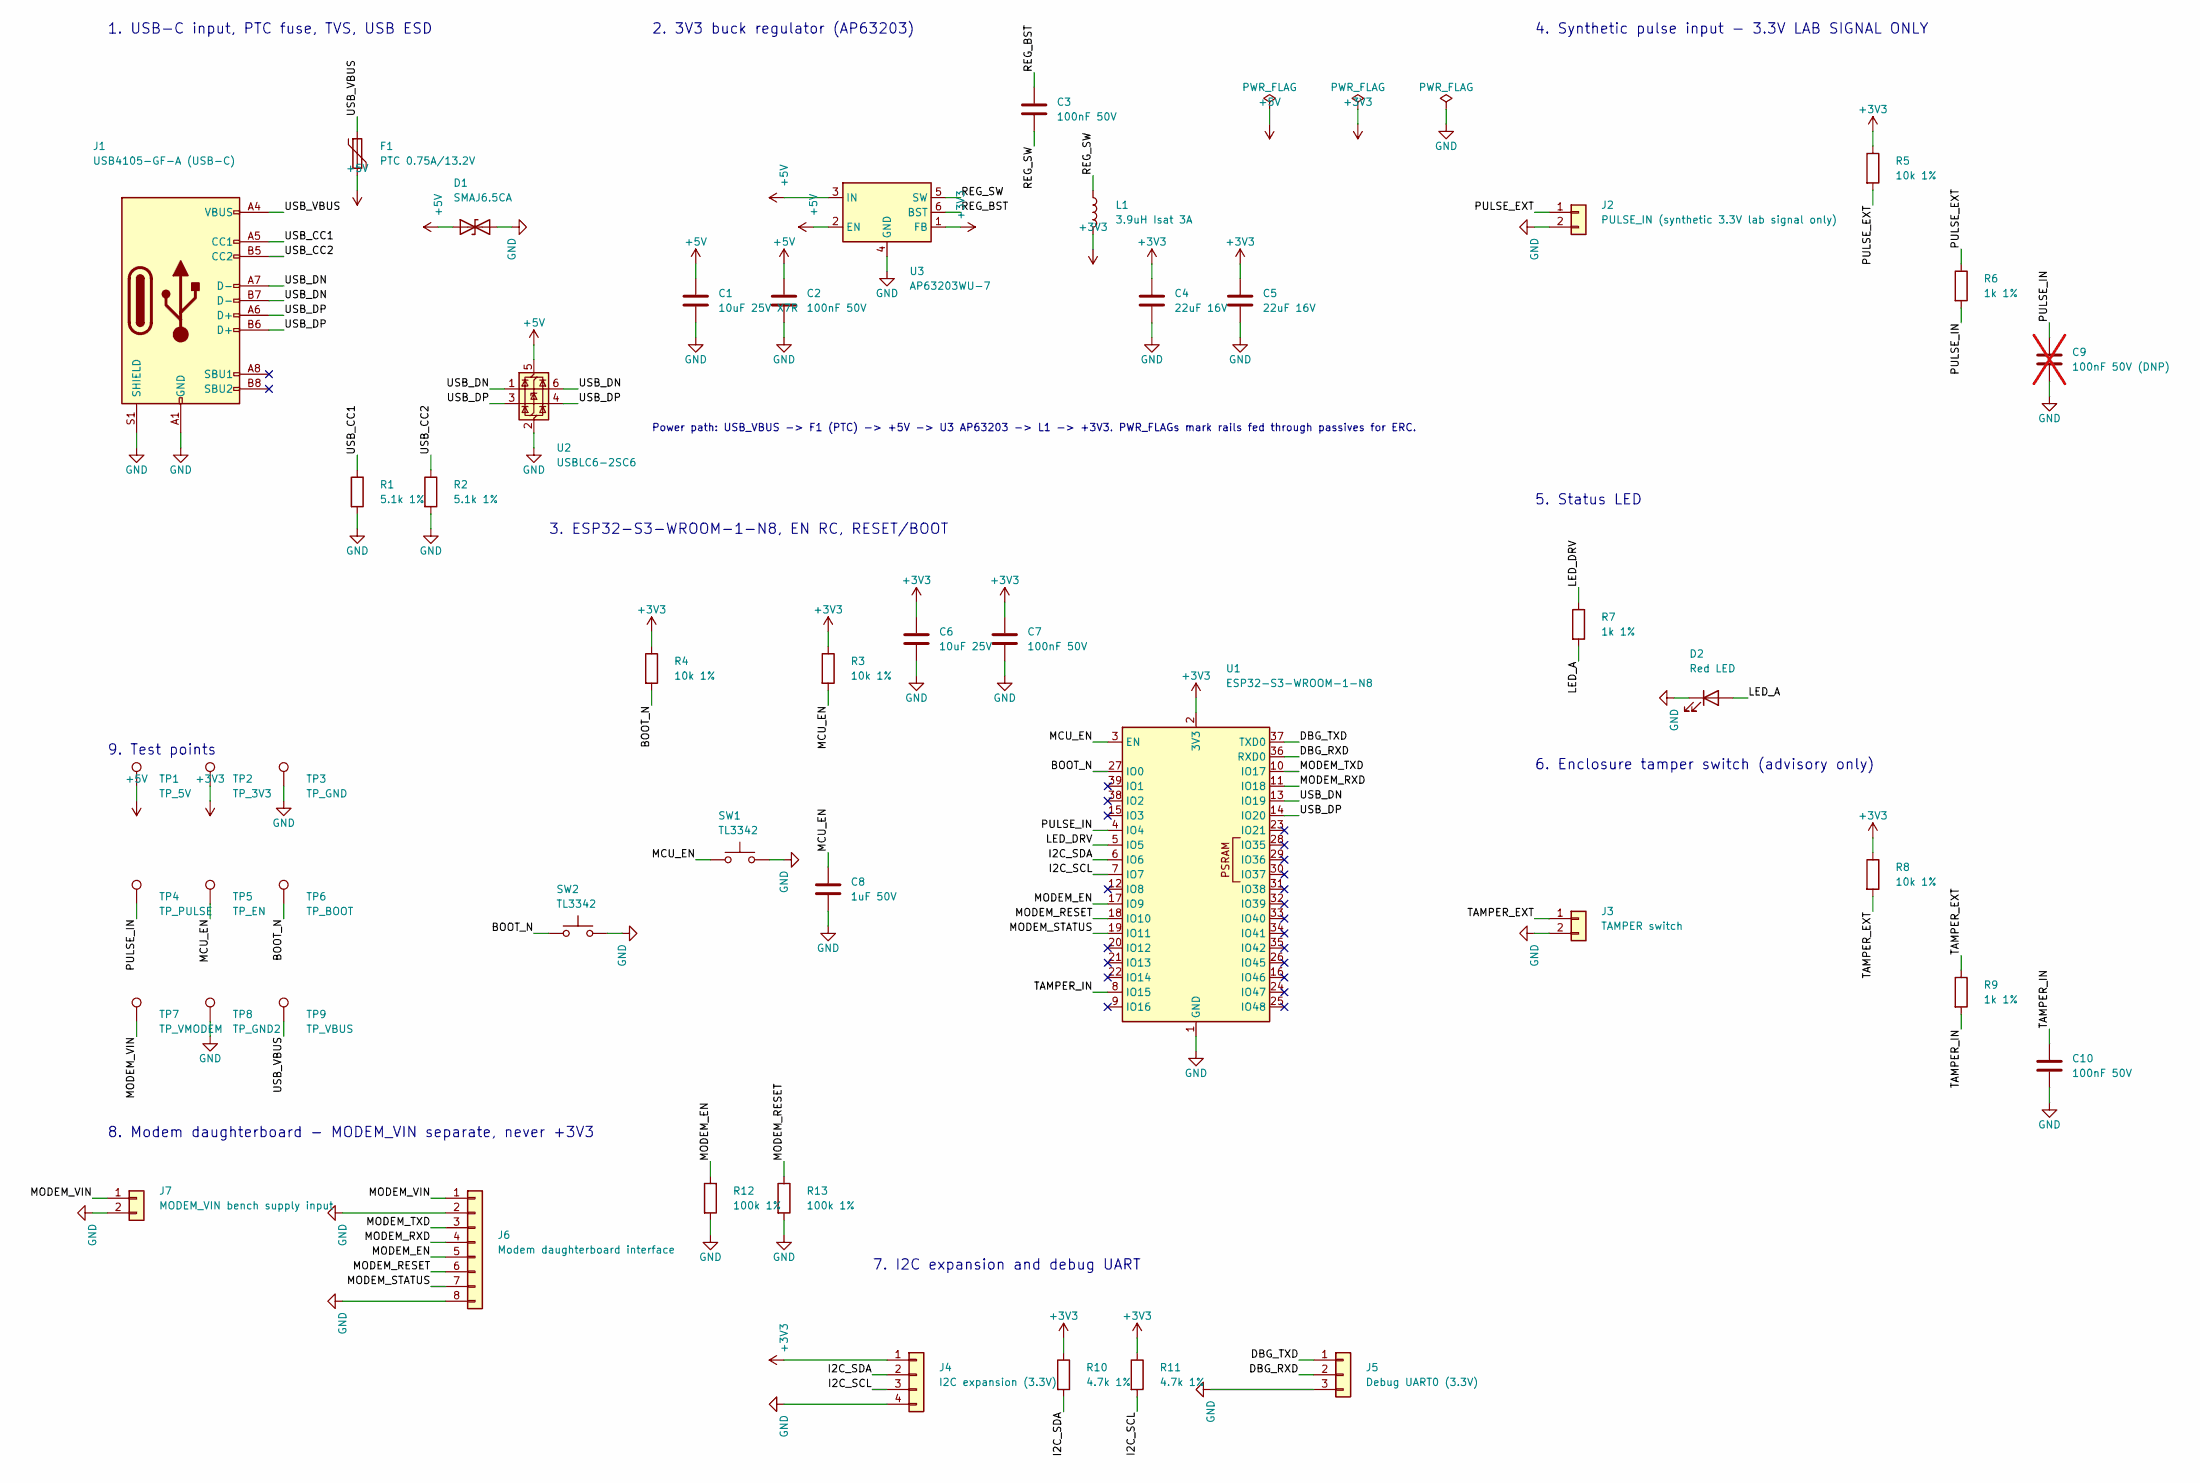
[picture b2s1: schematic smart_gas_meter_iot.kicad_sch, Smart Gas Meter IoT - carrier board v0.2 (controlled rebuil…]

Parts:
C1: 10uF 25V X7R; C_1206_3216Metric; MPN GRM31CR71E106KA12L; LCSC C77093
C2, C3, C7, C10: 100nF 50V; C_0603_1608Metric; MPN CC0603KRX7R9BB104; LCSC C14663
C4, C5: 22uF 16V; C_0805_2012Metric; MPN GRM21BR61C226ME44L; LCSC C86817
C6: 10uF 25V; C_0805_2012Metric; MPN CL21A106KAYNNNE; LCSC C15850
C8: 1uF 50V; C_0603_1608Metric; MPN CL10A105KB8NNNC; LCSC C15849
C9: 100nF 50V (DNP); C_0603_1608Metric; MPN CC0603KRX7R9BB104; LCSC C14663; not fitted
D1: SMAJ6.5CA; D_SMA; MPN SMAJ6.5CA; LCSC C5161320
D2: Red LED; LED_0603_1608Metric; MPN 19-213SURC/S530-A3/5T; LCSC C2986056
F1: PTC 0.75A/13.2V; Fuse_1206_3216Metric; MPN 1206L075/13.2WR; LCSC C207036
J1: USB4105-GF-A (USB-C); USB_C_Receptacle_GCT_USB4105-xx-A_16P_TopMnt_Horizontal; MPN USB4105-GF-A; LCSC C3020560
J2: PULSE_IN (synthetic 3.3V lab signal only); PinHeader_1x02_P2.54mm_Vertical; MPN generic
J3: TAMPER switch; PinHeader_1x02_P2.54mm_Vertical; MPN generic
J4: I2C expansion (3.3V); PinHeader_1x04_P2.54mm_Vertical; MPN generic
J5: Debug UART0 (3.3V); PinHeader_1x03_P2.54mm_Vertical; MPN generic
J6: Modem daughterboard interface; PinHeader_1x08_P2.54mm_Vertical; MPN generic
J7: MODEM_VIN bench supply input; PinHeader_1x02_P2.54mm_Vertical; MPN generic
L1: 3.9uH Isat 3A; L_Sunlord_SWPA4030S; MPN SWPA4030S3R9MT; LCSC C96899
R1, R2: 5.1k 1%; R_0603_1608Metric; MPN 0603WAF5101T5E; LCSC C23186
R3, R4, R5, R8: 10k 1%; R_0603_1608Metric; MPN 0603WAF1002T5E; LCSC C25804
R6, R7, R9: 1k 1%; R_0603_1608Metric; MPN 0603WAF1001T5E; LCSC C21190
R10, R11: 4.7k 1%; R_0603_1608Metric; MPN 0603WAF4701T5E; LCSC C23162
R12, R13: 100k 1%; R_0603_1608Metric; MPN 0603WAF1003T5E; LCSC C25803
SW1, SW2: TL3342; SW_SPST_TL3342; MPN TL3342F160QG; LCSC C2886898
TP1: TP_5V; TestPoint_Pad_D1.5mm; MPN generic
TP2: TP_3V3; TestPoint_Pad_D1.5mm; MPN generic
TP3: TP_GND; TestPoint_Pad_D1.5mm; MPN generic
TP4: TP_PULSE; TestPoint_Pad_D1.5mm; MPN generic
TP5: TP_EN; TestPoint_Pad_D1.5mm; MPN generic
TP6: TP_BOOT; TestPoint_Pad_D1.5mm; MPN generic
TP7: TP_VMODEM; TestPoint_Pad_D1.5mm; MPN generic
TP8: TP_GND2; TestPoint_Pad_D1.5mm; MPN generic
TP9: TP_VBUS; TestPoint_Pad_D1.5mm; MPN generic
U1: ESP32-S3-WROOM-1-N8; ESP32-S3-WROOM-1; MPN ESP32-S3-WROOM-1-N8; LCSC C2913198
U2: USBLC6-2SC6; SOT-23-6; MPN USBLC6-2SC6; LCSC C7519
U3: AP63203WU-7; TSOT-23-6; MPN AP63203WU-7; LCSC C780769

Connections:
+3V3: C4.1, C5.1, C6.1, C7.1, J4.1, L1.2, R3.1, R4.1, R5.1, R8.1, R10.1, R11.1, TP2.1, U1.2 (3V3), U3.1 (FB)
+5V: C1.1, C2.1, D1.1 (A1), F1.2, TP1.1, U2.5 (VBUS), U3.2 (EN), U3.3 (IN)
/BOOT_N: R4.2, SW2.1, TP6.1, U1.27 (IO0)
/DBG_RXD: J5.2, U1.36 (RXD0)
/DBG_TXD: J5.1, U1.37 (TXD0)
/I2C_SCL: J4.3, R11.2, U1.7 (IO7)
/I2C_SDA: J4.2, R10.2, U1.6 (IO6)
/LED_A: D2.2 (A), R7.2
/LED_DRV: R7.1, U1.5 (IO5)
/MCU_EN: C8.1, R3.2, SW1.1, TP5.1, U1.3 (EN)
/MODEM_EN: J6.5, R12.1, U1.17 (IO9)
/MODEM_RESET: J6.6, R13.1, U1.18 (IO10)
/MODEM_RXD: J6.4, U1.11 (IO18)
/MODEM_STATUS: J6.7, U1.19 (IO11)
/MODEM_TXD: J6.3, U1.10 (IO17)
/MODEM_VIN: J6.1, J7.1, TP7.1
/PULSE_EXT: J2.1, R5.2, R6.1
/PULSE_IN: C9.1, R6.2, TP4.1, U1.4 (IO4)
/REG_BST: C3.1, U3.6 (BST)
/REG_SW: C3.2, L1.1, U3.5 (SW)
/TAMPER_EXT: J3.1, R8.2, R9.1
/TAMPER_IN: C10.1, R9.2, U1.8 (IO15)
/USB_CC1: J1.A5 (CC1), R1.1
/USB_CC2: J1.B5 (CC2), R2.1
/USB_DN: J1.A7 (D-), J1.B7 (D-), U1.13 (IO19), U2.1 (I/O1), U2.6 (I/O1)
/USB_DP: J1.A6 (D+), J1.B6 (D+), U1.14 (IO20), U2.3 (I/O2), U2.4 (I/O2)
/USB_VBUS: F1.1, J1.A4 (VBUS), J1.A9 (VBUS), J1.B4 (VBUS), J1.B9 (VBUS), TP9.1
GND: C1.2, C2.2, C4.2, C5.2, C6.2, C7.2, C8.2, C9.2, C10.2, D1.2 (A2), D2.1 (K), J1.A1 (GND), J1.A12 (GND), J1.B1 (GND), J1.B12 (GND), J1.S1 (SHIELD), J2.2, J3.2, J4.4, J5.3, J6.2, J6.8, J7.2, R1.2, R2.2, R12.2, R13.2, SW1.2, SW2.2, TP3.1, TP8.1, U1.1 (GND), U1.40 (GND), U1.41 (GND), U2.2 (GND), U3.4 (GND)

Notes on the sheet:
1. USB-C input, PTC fuse, TVS, USB ESD
2. 3V3 buck regulator (AP63203)
3. ESP32-S3-WROOM-1-N8, EN RC, RESET/BOOT
4. Synthetic pulse input - 3.3V LAB SIGNAL ONLY
5. Status LED
6. Enclosure tamper switch (advisory only)
7. I2C expansion and debug UART
8. Modem daughterboard - MODEM_VIN separate, never +3V3
9. Test points
Power path: USB_VBUS -> F1 (PTC) -> +5V -> U3 AP63203 -> L1 -> +3V3. PWR_FLAGs mark rails fed through passives for ERC.
